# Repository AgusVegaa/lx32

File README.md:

<div align="center">
  <strong>PULSAR</strong><br>
  <em>LX32K keyboard processor stack: custom 32-bit core, RTL, golden model, LLVM backend, firmware, and host tools.</em>

  Overview | Firmware | Backend | RTL | Tools
</div>

This is the main source code repository for PULSAR. It contains the processor RTL, validation models, toolchain backend, firmware flow, and host utilities.

## Why PULSAR?

- **Determinism:** Hardware and firmware are designed for predictable timing and stable input scanning.
- **Full-stack control:** Custom ISA extensions, compiler backend, and simulation are all in one place.
- **Validation-first:** RTL, golden model, and tests keep behavior aligned across the stack.

## Quick Start

Run `make setup-backend`, then `make librust`.

## Getting Oriented

Start with `docs/README.md`, then `docs/firmware_guide.md` and `docs/backend.md`.

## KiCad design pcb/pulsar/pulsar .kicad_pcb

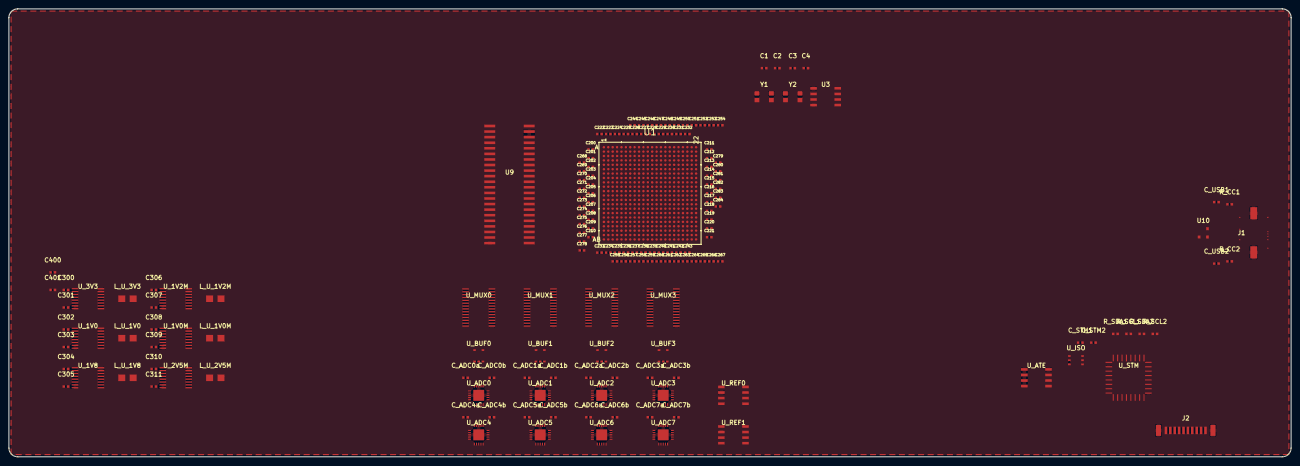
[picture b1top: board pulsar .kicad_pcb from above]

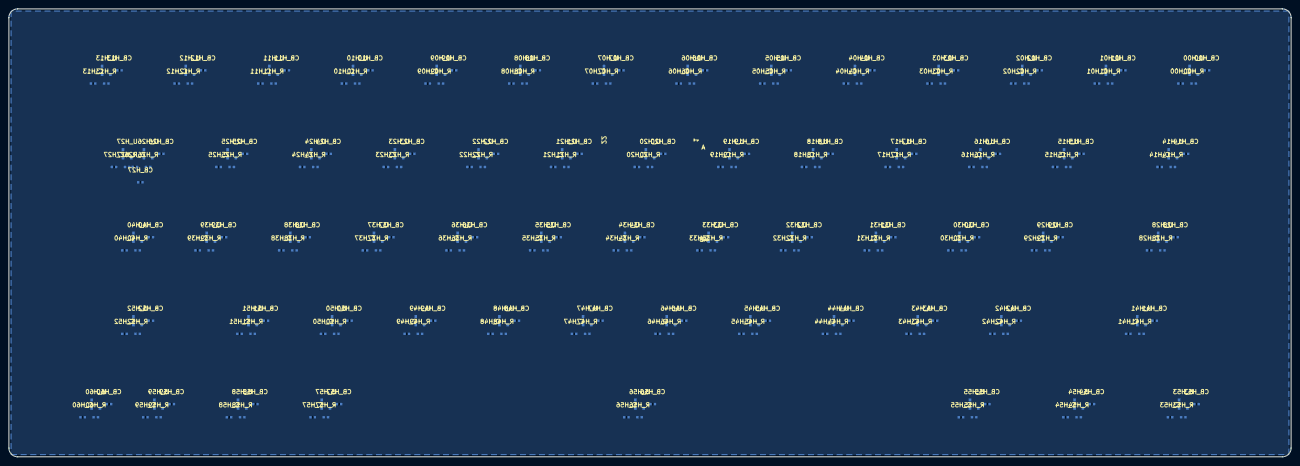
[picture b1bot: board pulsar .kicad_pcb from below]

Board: 16 copper layers, 292.0 x 102.0 mm, 414 parts (244 on the bottom side), 108 nets, no tracks yet.

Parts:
C1, C2, C3, C4: 12pF; C_0402
C200, C201, C202, C203, C204, C205, C206, C207, C208, C209, C210, C211, C212, C213, C214, C215, C216, C217, C218, C219, C220, C221, C222, C223, C224, C225, C226, C227, C228, C229, C230, C231, C232, C233, C234, C235, C236, C237, C238, C239, C240, C241, C242, C243, C244, C245, C246, C247, C248, C249, C250, C251, C252, C253, C254, C255, C256, C257, C258, C259, C260, C261, C262, C263, C264, C265, C266, C267, C268, C269, C270, C271, C272, C273, C274, C275, C276, C277, C278, C279, C280, C281, C282, C283, C284: 100nF; C_0402
C300, C302, C304, C306, C308, C310: 10uF 10V; C_0402
C301, C303, C305, C307, C309, C311: 10uF 6V; C_0402
C400, C401: 100uF 10V; C_0402
CB_H00, CB_H01, CB_H02, CB_H03, CB_H04, CB_H05, CB_H06, CB_H07, CB_H08, CB_H09, CB_H10, CB_H11, CB_H12, CB_H13, CB_H14, CB_H15, CB_H16, CB_H17, CB_H18, CB_H19, CB_H20, CB_H21, CB_H22, CB_H23, CB_H24, CB_H25, CB_H26, CB_H27, CB_H28, CB_H29, CB_H30, CB_H31, CB_H32, CB_H33, CB_H34, CB_H35, CB_H36, CB_H37, CB_H38, CB_H39, CB_H40, CB_H41, CB_H42, CB_H43, CB_H44, CB_H45, CB_H46, CB_H47, CB_H48, CB_H49, CB_H50, CB_H51, CB_H52, CB_H53, CB_H54, CB_H55, CB_H56, CB_H57, CB_H58, CB_H59, CB_H60: 100nF; C_0402
C_ADC0a, C_ADC1a, C_ADC2a, C_ADC3a, C_ADC4a, C_ADC5a, C_ADC6a, C_ADC7a: 100nF; C_0402
C_ADC0b, C_ADC1b, C_ADC2b, C_ADC3b, C_ADC4b, C_ADC5b, C_ADC6b, C_ADC7b: 1uF; C_0402
C_H00, C_H01, C_H02, C_H03, C_H04, C_H05, C_H06, C_H07, C_H08, C_H09, C_H10, C_H11, C_H12, C_H13, C_H14, C_H15, C_H16, C_H17, C_H18, C_H19, C_H20, C_H21, C_H22, C_H23, C_H24, C_H25, C_H26, C_H27, C_H28, C_H29, C_H30, C_H31, C_H32, C_H33, C_H34, C_H35, C_H36, C_H37, C_H38, C_H39, C_H40, C_H41, C_H42, C_H43, C_H44, C_H45, C_H46, C_H47, C_H48, C_H49, C_H50, C_H51, C_H52, C_H53, C_H54, C_H55, C_H56, C_H57, C_H58, C_H59, C_H60: 100nF; C_0402
C_STM1, C_STM2: 100nF; C_0402
C_USB1: 100nF; C_0402
C_USB2: 10uF; C_0402
J1: GX-C-065 USB-C; USB_C_Receptacle_HRO_TYPE-C-31-M-12
J2: FPC-10p 0.5mm; Molex_503480-1000_1x10-1MP_P1.00mm
L_U_1V0, L_U_1V0M, L_U_1V2M, L_U_1V8, L_U_2V5M, L_U_3V3: 2.2uH; L_2520_6332Metric
R_CC1, R_CC2: 5.1k; C_0402
R_H00, R_H01, R_H02, R_H03, R_H04, R_H05, R_H06, R_H07, R_H08, R_H09, R_H10, R_H11, R_H12, R_H13, R_H14, R_H15, R_H16, R_H17, R_H18, R_H19, R_H20, R_H21, R_H22, R_H23, R_H24, R_H25, R_H26, R_H27, R_H28, R_H29, R_H30, R_H31, R_H32, R_H33, R_H34, R_H35, R_H36, R_H37, R_H38, R_H39, R_H40, R_H41, R_H42, R_H43, R_H44, R_H45, R_H46, R_H47, R_H48, R_H49, R_H50, R_H51, R_H52, R_H53, R_H54, R_H55, R_H56, R_H57, R_H58, R_H59, R_H60: 10k; C_0402
R_SCL1, R_SCL2: 4.7k; C_0402
R_SDA1, R_SDA2: 4.7k; C_0402
U1: XC7A200T-2FBG484I; XC7A200T_FBG484
U3: W25Q128JVSIQ; SOIC-8_3.9x4.9mm_P1.27mm
U9: IS61WV102416BLL; SRAM_SOJ-44
U10: PRTR5V0U2X; SOT-23
U_1V0: TPS62130 +1V0; TSSOP-16_4.4x5mm_P0.65mm
U_1V0M: TPS62130 +1V0_MGT; TSSOP-16_4.4x5mm_P0.65mm
U_1V2M: TPS62130 +1V2_MGT; TSSOP-16_4.4x5mm_P0.65mm
U_1V8: TPS62130 +1V8; TSSOP-16_4.4x5mm_P0.65mm
U_2V5M: TPS62130 +2V5_MGT; TSSOP-16_4.4x5mm_P0.65mm
U_3V3: TPS62133 +3V3; TSSOP-16_4.4x5mm_P0.65mm
U_ADC0, U_ADC1, U_ADC2, U_ADC3, U_ADC4, U_ADC5, U_ADC6, U_ADC7: AD7689BCPZ; LFCSP-20-1EP_4x4mm_P0.5mm
U_ATE: ATECC608B-MAHDA-S; SOIC-8_3.9x4.9mm_P1.27mm
U_BUF0, U_BUF1, U_BUF2, U_BUF3: OPA2365AIDBVT; SOT-23-5
U_H00, U_H01, U_H02, U_H03, U_H04, U_H05, U_H06, U_H07, U_H08, U_H09, U_H10, U_H11, U_H12, U_H13, U_H14, U_H15, U_H16, U_H17, U_H18, U_H19, U_H20, U_H21, U_H22, U_H23, U_H24, U_H25, U_H26, U_H27, U_H28, U_H29, U_H30, U_H31, U_H32, U_H33, U_H34, U_H35, U_H36, U_H37, U_H38, U_H39, U_H40, U_H41, U_H42, U_H43, U_H44, U_H45, U_H46, U_H47, U_H48, U_H49, U_H50, U_H51, U_H52, U_H53, U_H54, U_H55, U_H56, U_H57, U_H58, U_H59, U_H60: DRV5055A2QDBZR; SOT-23
U_ISO: ISO1540QDRQ1; SOT-23-6
U_MUX0, U_MUX1, U_MUX2, U_MUX3: ADG1606BRUZ; TSSOP-28_4.4x9.7mm_P0.65mm
U_REF0, U_REF1: REF5025ID; SOIC-8_3.9x4.9mm_P1.27mm
U_STM: STM32L052K8T6; LQFP-32_7x7mm_P0.8mm
Y1: 50MHz_XTAL; Crystal_SMD_3225-4Pin_3.2x2.5mm
Y2: 48MHz_XTAL; Crystal_SMD_3225-4Pin_3.2x2.5mm

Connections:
+1V0: C200.1, C201.1, C202.1, C203.1, C204.1, C205.1, C206.1, C207.1, C208.1, C209.1, C210.1, C211.1, C212.1, C213.1, C214.1, C215.1, C216.1, C217.1, C218.1, C219.1, C220.1, C221.1, C222.1, C223.1, C224.1, C225.1, C226.1, C227.1, C249.1, C250.1, C251.1, C252.1, C253.1, C254.1, C303.1, L_U_1V0.2, U1.H8, U1.H10, U1.J7, U1.J9, U1.J11, U1.K8, U1.L7, U1.L11, U1.M8, U1.N7, U1.N11, U1.P8, U1.P10, U1.R7, U1.R9, U1.T8, U1.T10, U_1V0.9
+1V0_MGT: C237.1, C238.1, C239.1, C240.1, C268.1, C269.1, C270.1, C271.1, C272.1, C273.1, C279.1, C280.1, C281.1, C282.1, C283.1, C284.1, C309.1, L_U_1V0M.2, U1.D6, U1.D10, U1.E8, U1.F7, U1.F9, U_1V0M.9
+1V2_MGT: C241.1, C242.1, C243.1, C274.1, C275.1, C276.1, C277.1, C278.1, C307.1, L_U_1V2M.2, U1.B5, U1.B7, U1.B9, U1.B11, U1.C4, U1.C8, U_1V2M.9
+1V8: C233.1, C234.1, C235.1, C236.1, C262.1, C263.1, C264.1, C265.1, C266.1, C267.1, C305.1, C_STM2.1, L_U_1V8.2, R_SCL2.2, R_SDA2.2, U1.F12, U1.H12, U1.K10, U1.K12, U1.M12, U1.P12, U1.R11, U1.T12, U_1V8.9, U_ATE.7
+2V5_MGT: C255.1, C256.1, C257.1, C258.1, C259.1, C260.1, C261.1, C311.1, L_U_2V5M.2, U_2V5M.9
+2V5_REF: U_ADC0.7, U_ADC1.7, U_ADC2.7, U_ADC3.7, U_ADC4.7, U_ADC5.7, U_ADC6.7, U_ADC7.7, U_REF0.5, U_REF0.8, U_REF1.5, U_REF1.8
+3V3: C228.1, C229.1, C230.1, C231.1, C232.1, C244.1, C245.1, C246.1, C247.1, C248.1, C301.1, CB_H00.1, CB_H01.1, CB_H02.1, CB_H03.1, CB_H04.1, CB_H05.1, CB_H06.1, CB_H07.1, CB_H08.1, CB_H09.1, CB_H10.1, CB_H11.1, CB_H12.1, CB_H13.1, CB_H14.1, CB_H15.1, CB_H16.1, CB_H17.1, CB_H18.1, CB_H19.1, CB_H20.1, CB_H21.1, CB_H22.1, CB_H23.1, CB_H24.1, CB_H25.1, CB_H26.1, CB_H27.1, CB_H28.1, CB_H29.1, CB_H30.1, CB_H31.1, CB_H32.1, CB_H33.1, CB_H34.1, CB_H35.1, CB_H36.1, CB_H37.1, CB_H38.1, CB_H39.1, CB_H40.1, CB_H41.1, CB_H42.1, CB_H43.1, CB_H44.1, CB_H45.1, CB_H46.1, CB_H47.1, CB_H48.1, CB_H49.1, CB_H50.1, CB_H51.1, CB_H52.1, CB_H53.1, CB_H54.1, CB_H55.1, CB_H56.1, CB_H57.1, CB_H58.1, CB_H59.1, CB_H60.1, C_ADC0a.1, C_ADC0b.1, C_ADC1a.1, C_ADC1b.1, C_ADC2a.1, C_ADC2b.1, C_ADC3a.1, C_ADC3b.1, C_ADC4a.1, C_ADC4b.1, C_ADC5a.1, C_ADC5b.1, C_ADC6a.1, C_ADC6b.1, C_ADC7a.1, C_ADC7b.1, C_STM1.1, L_U_3V3.2, R_SCL1.2, R_SDA1.2, U1.A17, U1.AA7, U1.AA17, U1.AB4, U1.AB14, U1.B14, U1.C1, U1.C21, U1.D18, U1.E12, U1.E15, U1.F2, U1.F22, U1.G19, U1.H6, U1.H16, U1.J3, U1.J13, U1.K20, U1.L17, U1.M4, U1.M14, U1.N1, U1.N21, U1.P18, U1.R5, U1.R15, U1.T2, U1.T22, U1.U19, U1.V6, U1.V16, U1.W3, U1.W13, U1.Y10, U1.Y20, U3.2, U9.44, U_3V3.9, U_BUF0.5, U_BUF1.5, U_BUF2.5, U_BUF3.5, U_H00.3, U_H01.3, U_H02.3, U_H03.3, U_H04.3, U_H05.3, U_H06.3, U_H07.3, U_H08.3, U_H09.3, U_H10.3, U_H11.3, U_H12.3, U_H13.3, U_H14.3, U_H15.3, U_H16.3, U_H17.3, U_H18.3, U_H19.3, U_H20.3, U_H21.3, U_H22.3, U_H23.3, U_H24.3, U_H25.3, U_H26.3, U_H27.3, U_H28.3, U_H29.3, U_H30.3, U_H31.3, U_H32.3, U_H33.3, U_H34.3, U_H35.3, U_H36.3, U_H37.3, U_H38.3, U_H39.3, U_H40.3, U_H41.3, U_H42.3, U_H43.3, U_H44.3, U_H45.3, U_H46.3, U_H47.3, U_H48.3, U_H49.3, U_H50.3, U_H51.3, U_H52.3, U_H53.3, U_H54.3, U_H55.3, U_H56.3, U_H57.3, U_H58.3, U_H59.3, U_H60.3, U_ISO.6, U_MUX0.24, U_MUX1.24, U_MUX2.24, U_MUX3.24, U_REF0.1, U_REF0.4, U_REF0.6, U_REF1.1, U_REF1.4, U_REF1.6, U_STM.1, U_STM.32
ADC1_CNV: U_ADC0.4, U_ADC4.4
ADC1_SCK: U_ADC0.1, U_ADC4.1
ADC1_SDI: U_ADC0.3, U_ADC4.3
ADC1_SDO: U_ADC0.2, U_ADC4.2
ADC2_CNV: U_ADC1.4, U_ADC5.4
ADC2_SCK: U_ADC1.1, U_ADC5.1
ADC2_SDI: U_ADC1.3, U_ADC5.3
ADC2_SDO: U_ADC1.2, U_ADC5.2
ADC3_CNV: U_ADC2.4, U_ADC6.4
ADC3_SCK: U_ADC2.1, U_ADC6.1
ADC3_SDI: U_ADC2.3, U_ADC6.3
ADC3_SDO: U_ADC2.2, U_ADC6.2
ADC4_CNV: U_ADC3.4, U_ADC7.4
ADC4_SCK: U_ADC3.1, U_ADC7.1
ADC4_SDI: U_ADC3.3, U_ADC7.3
ADC4_SDO: U_ADC3.2, U_ADC7.2
CC1: J1.A5, R_CC1.1
CC2: J1.B8, R_CC2.1
CLK_48M: C3.1, C4.1, Y2.1, Y2.2
CLK_50M: C1.1, C2.1, Y1.1, Y1.2
FIDO2_SCL: R_SCL1.1, U_ISO.2, U_STM.29
FIDO2_SDA: R_SDA1.1, U_ISO.1, U_STM.30
GND: C1.2, C2.2, C3.2, C4.2, C200.2, C201.2, C202.2, C203.2, C204.2, C205.2, C206.2, C207.2, C208.2, C209.2, C210.2, C211.2, C212.2, C213.2, C214.2, C215.2, C216.2, C217.2, C218.2, C219.2, C220.2, C221.2, C222.2, C223.2, C224.2, C225.2, C226.2, C227.2, C228.2, C229.2, C230.2, C231.2, C232.2, C233.2, C234.2, C235.2, C236.2, C237.2, C238.2, C239.2, C240.2, C241.2, C242.2, C243.2, C244.2, C245.2, C246.2, C247.2, C248.2, C249.2, C250.2, C251.2, C252.2, C253.2, C254.2, C255.2, C256.2, C257.2, C258.2, C259.2, C260.2, C261.2, C262.2, C263.2, C264.2, C265.2, C266.2, C267.2, C268.2, C269.2, C270.2, C271.2, C272.2, C273.2, C274.2, C275.2, C276.2, C277.2, C278.2, C279.2, C280.2, C281.2, C282.2, C283.2, C284.2, C300.2, C301.2, C302.2, C303.2, C304.2, C305.2, C306.2, C307.2, C308.2, C309.2, C310.2, C311.2, C400.2, C401.2, CB_H00.2, CB_H01.2, CB_H02.2, CB_H03.2, CB_H04.2, CB_H05.2, CB_H06.2, CB_H07.2, CB_H08.2, CB_H09.2, CB_H10.2, CB_H11.2, CB_H12.2, CB_H13.2, CB_H14.2, CB_H15.2, CB_H16.2, CB_H17.2, CB_H18.2, CB_H19.2, CB_H20.2, CB_H21.2, CB_H22.2, CB_H23.2, CB_H24.2, CB_H25.2, CB_H26.2, CB_H27.2, CB_H28.2, CB_H29.2, CB_H30.2, CB_H31.2, CB_H32.2, CB_H33.2, CB_H34.2, CB_H35.2, CB_H36.2, CB_H37.2, CB_H38.2, CB_H39.2, CB_H40.2, CB_H41.2, CB_H42.2, CB_H43.2, CB_H44.2, CB_H45.2, CB_H46.2, CB_H47.2, CB_H48.2, CB_H49.2, CB_H50.2, CB_H51.2, CB_H52.2, CB_H53.2, CB_H54.2, CB_H55.2, CB_H56.2, CB_H57.2, CB_H58.2, CB_H59.2, CB_H60.2, C_ADC0a.2, C_ADC0b.2, C_ADC1a.2, C_ADC1b.2, C_ADC2a.2, C_ADC2b.2, C_ADC3a.2, C_ADC3b.2, C_ADC4a.2, C_ADC4b.2, C_ADC5a.2, C_ADC5b.2, C_ADC6a.2, C_ADC6b.2, C_ADC7a.2, C_ADC7b.2, C_H00.2, C_H01.2, C_H02.2, C_H03.2, C_H04.2, C_H05.2, C_H06.2, C_H07.2, C_H08.2, C_H09.2, C_H10.2, C_H11.2, C_H12.2, C_H13.2, C_H14.2, C_H15.2, C_H16.2, C_H17.2, C_H18.2, C_H19.2, C_H20.2, C_H21.2, C_H22.2, C_H23.2, C_H24.2, C_H25.2, C_H26.2, C_H27.2, C_H28.2, C_H29.2, C_H30.2, C_H31.2, C_H32.2, C_H33.2, C_H34.2, C_H35.2, C_H36.2, C_H37.2, C_H38.2, C_H39.2, C_H40.2, C_H41.2, C_H42.2, C_H43.2, C_H44.2, C_H45.2, C_H46.2, C_H47.2, C_H48.2, C_H49.2, C_H50.2, C_H51.2, C_H52.2, C_H53.2, C_H54.2, C_H55.2, C_H56.2, C_H57.2, C_H58.2, C_H59.2, C_H60.2, C_STM1.2, C_STM2.2, C_USB1.2, C_USB2.2, J1.A1, J1.A12, J1.B1, J1.B12, J1.SH1, J1.SH2, J2.MP1, J2.MP2, R_CC1.2, R_CC2.2, U1.A2, U1.A3, U1.A5, U1.A7, U1.A9, U1.A11, U1.A12, U1.A22, U1.AA2, U1.AA12, U1.AA22, U1.AB9, U1.AB19, U1.B3, U1.B12, U1.B19, U1.C3, U1.C6, U1.C10, U1.C12, U1.C16, U1.D3, U1.D4, U1.D8, U1.D12, U1.D13, U1.E4, U1.E5, U1.E7, U1.E9, U1.E11, U1.E20, U1.F5, U1.F11, U1.F17, U1.G5, U1.G6, U1.G7, U1.G8, U1.G9, U1.G10, U1.G12, U1.G14, U1.H1, U1.H7, U1.H9, U1.H11, U1.H21, U1.J8, U1.J10, U1.J12, U1.J18, U1.K5, U1.K7, U1.K9, U1.K11, U1.K15, U1.L2, U1.L8, U1.L9, U1.L22, U1.M7, U1.M11, U1.M19, U1.N6, U1.N8, U1.N16, U1.P3, U1.P7, U1.P9, U1.P11, U1.P13, U1.R8, U1.R10, U1.R12, U1.R20, U1.T7, U1.T9, U1.T11, U1.T17, U1.U4, U1.U14, U1.V1, U1.V11, U1.V21, U1.W8, U1.W18, U1.Y5, U1.Y15, U3.1, U3.4, U9.22, U9.42, U9.43, U10.2, U_1V0.7, U_1V0.8, U_1V0.15, U_1V0.16, U_1V0M.7, U_1V0M.8, U_1V0M.15, U_1V0M.16, U_1V2M.7, U_1V2M.8, U_1V2M.15, U_1V2M.16, U_1V8.7, U_1V8.8, U_1V8.15, U_1V8.16, U_2V5M.7, U_2V5M.8, U_2V5M.15, U_2V5M.16, U_3V3.7, U_3V3.8, U_3V3.15, U_3V3.16, U_ADC0.8, U_ADC0.11, U_ADC0.12, U_ADC0.13, U_ADC0.14, U_ADC0.15, U_ADC0.16, U_ADC0.17, U_ADC0.18, U_ADC0.EP, U_ADC1.8, U_ADC1.11, U_ADC1.12, U_ADC1.13, U_ADC1.14, U_ADC1.15, U_ADC1.16, U_ADC1.17, U_ADC1.18, U_ADC1.EP, U_ADC2.8, U_ADC2.11, U_ADC2.12, U_ADC2.13, U_ADC2.14, U_ADC2.15, U_ADC2.16, U_ADC2.17, U_ADC2.18, U_ADC2.EP, U_ADC3.8, U_ADC3.11, U_ADC3.12, U_ADC3.13, U_ADC3.14, U_ADC3.15, U_ADC3.16, U_ADC3.17, U_ADC3.18, U_ADC3.EP, U_ADC4.8, U_ADC4.11, U_ADC4.12, U_ADC4.13, U_ADC4.14, U_ADC4.15, U_ADC4.16, U_ADC4.17, U_ADC4.18, U_ADC4.EP, U_ADC5.8, U_ADC5.11, U_ADC5.12, U_ADC5.13, U_ADC5.14, U_ADC5.15, U_ADC5.16, U_ADC5.17, U_ADC5.18, U_ADC5.EP, U_ADC6.8, U_ADC6.11, U_ADC6.12, U_ADC6.13, U_ADC6.14, U_ADC6.15, U_ADC6.16, U_ADC6.17, U_ADC6.18, U_ADC6.EP, U_ADC7.8, U_ADC7.11, U_ADC7.12, U_ADC7.13, U_ADC7.14, U_ADC7.15, U_ADC7.16, U_ADC7.17, U_ADC7.18, U_ADC7.EP, U_ATE.1, U_ATE.2, U_ATE.3, U_ATE.4, U_ATE.8, U_BUF0.2, U_BUF1.2, U_BUF2.2, U_BUF3.2, U_H00.2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
HALL0: R_H00.1, U_H00.1, U_MUX0.1
HALL1: R_H01.1, U_H01.1, U_MUX0.2
HALL2: R_H02.1, U_H02.1, U_MUX0.3
HALL3: R_H03.1, U_H03.1, U_MUX0.4
HALL4: R_H04.1, U_H04.1, U_MUX0.5
HALL5: R_H05.1, U_H05.1, U_MUX0.6
HALL6: R_H06.1, U_H06.1, U_MUX0.7
HALL7: R_H07.1, U_H07.1, U_MUX0.8
HALL8: R_H08.1, U_H08.1, U_MUX0.9
HALL9: R_H09.1, U_H09.1, U_MUX0.10
HALL10: R_H10.1, U_H10.1, U_MUX0.11
HALL11: R_H11.1, U_H11.1, U_MUX0.12
HALL12: R_H12.1, U_H12.1, U_MUX0.13
HALL13: R_H13.1, U_H13.1, U_MUX0.14
HALL14: R_H14.1, U_H14.1, U_MUX0.16
HALL15: R_H15.1, U_H15.1, U_MUX0.17
HALL16: R_H16.1, U_H16.1, U_MUX1.1
HALL17: R_H17.1, U_H17.1, U_MUX1.2
HALL18: R_H18.1, U_H18.1, U_MUX1.3
HALL19: R_H19.1, U_H19.1, U_MUX1.4
HALL20: R_H20.1, U_H20.1, U_MUX1.5
HALL21: R_H21.1, U_H21.1, U_MUX1.6
HALL22: R_H22.1, U_H22.1, U_MUX1.7
HALL23: R_H23.1, U_H23.1, U_MUX1.8
HALL24: R_H24.1, U_H24.1, U_MUX1.9
HALL25: R_H25.1, U_H25.1, U_MUX1.10
HALL26: R_H26.1, U_H26.1, U_MUX1.11
HALL27: R_H27.1, U_H27.1, U_MUX1.12
HALL28: R_H28.1, U_H28.1, U_MUX1.13
HALL29: R_H29.1, U_H29.1, U_MUX1.14
HALL30: R_H30.1, U_H30.1, U_MUX1.16
HALL31: R_H31.1, U_H31.1, U_MUX1.17
HALL32: R_H32.1, U_H32.1, U_MUX2.1
HALL33: R_H33.1, U_H33.1, U_MUX2.2
HALL34: R_H34.1, U_H34.1, U_MUX2.3
HALL35: R_H35.1, U_H35.1, U_MUX2.4
HALL36: R_H36.1, U_H36.1, U_MUX2.5
HALL37: R_H37.1, U_H37.1, U_MUX2.6
HALL38: R_H38.1, U_H38.1, U_MUX2.7
HALL39: R_H39.1, U_H39.1, U_MUX2.8
HALL40: R_H40.1, U_H40.1, U_MUX2.9
HALL41: R_H41.1, U_H41.1, U_MUX2.10
HALL42: R_H42.1, U_H42.1, U_MUX2.11
HALL43: R_H43.1, U_H43.1, U_MUX2.12
HALL44: R_H44.1, U_H44.1, U_MUX2.13
HALL45: R_H45.1, U_H45.1, U_MUX2.14
HALL46: R_H46.1, U_H46.1, U_MUX2.16
HALL47: R_H47.1, U_H47.1, U_MUX2.17
HALL48: R_H48.1, U_H48.1, U_MUX3.1
HALL49: R_H49.1, U_H49.1, U_MUX3.2
HALL50: R_H50.1, U_H50.1, U_MUX3.3
HALL51: R_H51.1, U_H51.1, U_MUX3.4
HALL52: R_H52.1, U_H52.1, U_MUX3.5
HALL53: R_H53.1, U_H53.1, U_MUX3.6
HALL54: R_H54.1, U_H54.1, U_MUX3.7
HALL55: R_H55.1, U_H55.1, U_MUX3.8
HALL56: R_H56.1, U_H56.1, U_MUX3.9
HALL57: R_H57.1, U_H57.1, U_MUX3.10
HALL58: R_H58.1, U_H58.1, U_MUX3.11
HALL59: R_H59.1, U_H59.1, U_MUX3.12
HALL60: R_H60.1, U_H60.1, U_MUX3.13
I2C_SCL: R_SCL2.1, U_ATE.5, U_ISO.4
I2C_SDA: R_SDA2.1, U_ATE.6, U_ISO.5
MUX0_D: U_BUF0.3, U_MUX0.23
MUX0_OUT: U_ADC0.9, U_ADC4.9, U_BUF0.1, U_BUF0.4
MUX1_D: U_BUF1.3, U_MUX1.23
MUX1_OUT: U_ADC1.9, U_ADC5.9, U_BUF1.1, U_BUF1.4
MUX2_D: U_BUF2.3, U_MUX2.23
MUX2_OUT: U_ADC2.9, U_ADC6.9, U_BUF2.1, U_BUF2.4
MUX3_D: U_BUF3.3, U_MUX3.23
MUX3_OUT: U_ADC3.9, U_ADC7.9, U_BUF3.1, U_BUF3.4
MUX_A0: U_MUX0.18, U_MUX1.18, U_MUX2.18, U_MUX3.18
MUX_A1: U_MUX0.19, U_MUX1.19, U_MUX2.19, U_MUX3.19
MUX_A2: U_MUX0.20, U_MUX1.20, U_MUX2.20, U_MUX3.20
MUX_A3: U_MUX0.21, U_MUX1.21, U_MUX2.21, U_MUX3.21
USB_DM_RAW: J1.A7, J1.B7, U10.3, U_STM.18
USB_DP_RAW: J1.A6, J1.B6, U10.1, U_STM.19
VBUS: C300.1, C302.1, C304.1, C306.1, C308.1, C310.1, C400.1, C401.1, C_USB1.1, C_USB2.1, J1.A4, J1.B9, L_U_1V0.1, L_U_1V0M.1, L_U_1V2M.1, L_U_1V8.1, L_U_2V5M.1, L_U_3V3.1, U_1V0.1, U_1V0M.1, U_1V2M.1, U_1V8.1, U_2V5M.1, U_3V3.1

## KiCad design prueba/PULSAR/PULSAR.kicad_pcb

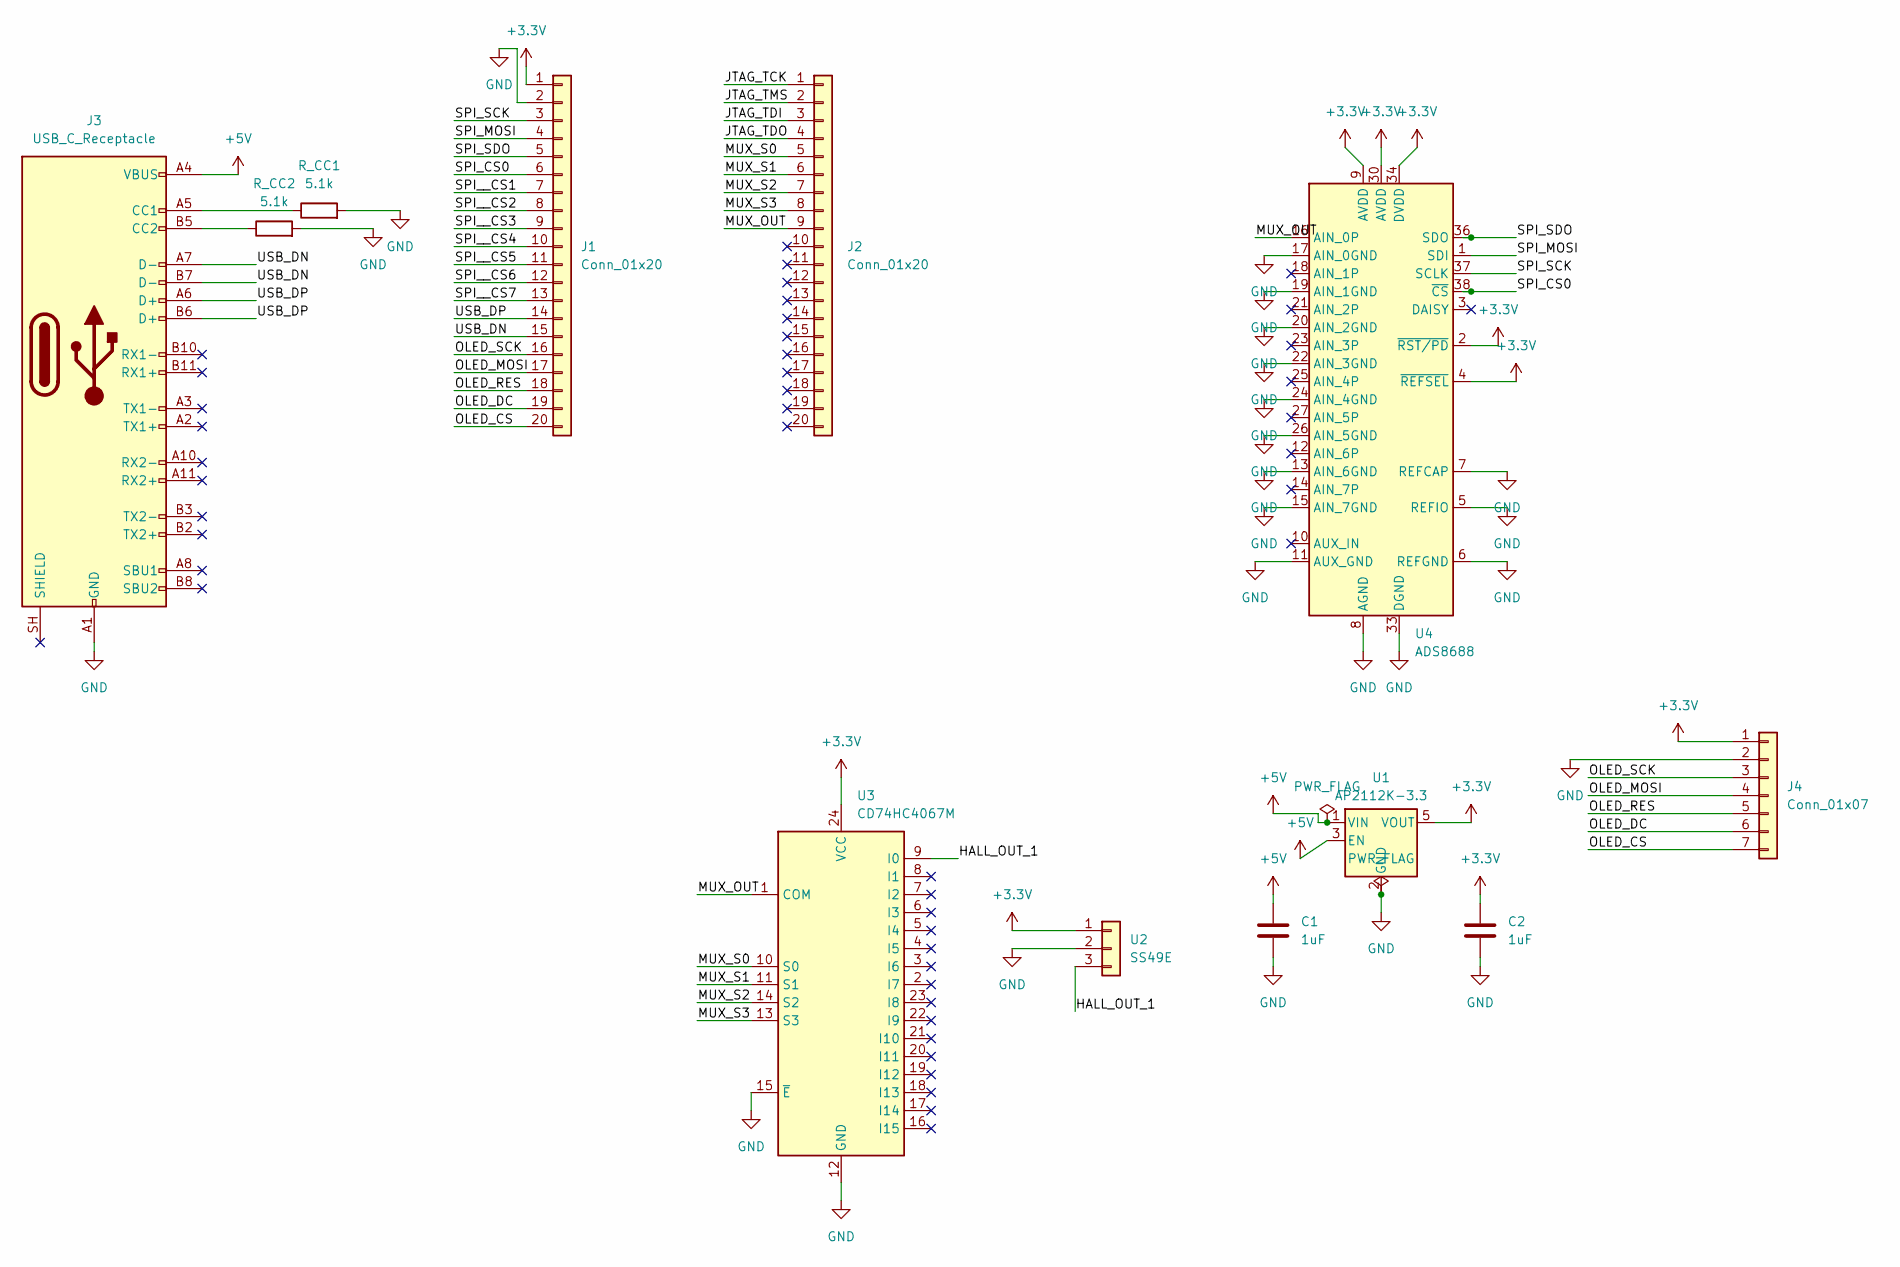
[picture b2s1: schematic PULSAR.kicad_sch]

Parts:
C1, C2: 1uF; C_0805_2012Metric; LCSC C52923
J1, J2: Conn_01x20; PinHeader_1x20_P2.54mm_Vertical
J3: USB_C_Receptacle; USB_C_Receptacle_GCT_USB4115-03-C; LCSC C168688
J4: Conn_01x07; PinHeader_1x07_P2.54mm_Vertical
R_CC1, R_CC2: 5.1k; R_0402_1005Metric; LCSC C23186
U1: AP2112K-3.3; SOT-23-5; LCSC C51118
U2: SS49E; TO-92_Inline; LCSC C85697
U3: CD74HC4067M; SSOP-24_5.3x8.2mm_P0.65mm; LCSC C98457
U4: ADS8688; TSSOP-38_4.4x9.7mm_P0.5mm; LCSC C1542682

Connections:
+3.3V: C2.1, J1.1, J4.1, U1.5 (VOUT), U2.1, U3.24 (VCC), U4.2 (~RST/PD), U4.4 (~REFSEL), U4.9 (AVDD), U4.30 (AVDD), U4.34 (DVDD)
+5V: C1.1, J3.A4 (VBUS), J3.A9 (VBUS), J3.B4 (VBUS), J3.B9 (VBUS), U1.1 (VIN), U1.3 (EN)
/HALL_OUT_1: U2.3, U3.9 (I0)
/JTAG_TCK: J2.1
/JTAG_TDI: J2.3
/JTAG_TDO: J2.4
/JTAG_TMS: J2.2
/MUX_OUT: J2.9, U3.1 (COM), U4.16 (AIN_0P)
/MUX_S0: J2.5, U3.10 (S0)
/MUX_S1: J2.6, U3.11 (S1)
/MUX_S2: J2.7, U3.14 (S2)
/MUX_S3: J2.8, U3.13 (S3)
/OLED_CS: J1.20, J4.7
/OLED_DC: J1.19, J4.6
/OLED_MOSI: J1.17, J4.4
/OLED_RES: J1.18, J4.5
/OLED_SCK: J1.16, J4.3
/SPI_CS0: J1.6, U4.38 (~CS)
/SPI_MOSI: J1.4, U4.1 (SDI)
/SPI_SCK: J1.3, U4.37 (SCLK)
/SPI_SDO: J1.5, U4.36 (SDO)
/SPI__CS1: J1.7
/SPI__CS2: J1.8
/SPI__CS3: J1.9
/SPI__CS4: J1.10
/SPI__CS5: J1.11
/SPI__CS6: J1.12
/SPI__CS7: J1.13
/USB_DN: J1.15, J3.A7 (D-), J3.B7 (D-)
/USB_DP: J1.14, J3.A6 (D+), J3.B6 (D+)
GND: C1.2, C2.2, J1.2, J3.A1 (GND), J3.A12 (GND), J3.B1 (GND), J3.B12 (GND), J4.2, R_CC1.2, R_CC2.2, U1.2 (GND), U2.2, U3.12 (GND), U3.15 (~E), U4.5 (REFIO), U4.6 (REFGND), U4.7 (REFCAP), U4.8 (AGND), U4.11 (AUX_GND), U4.13 (AIN_6GND), U4.15 (AIN_7GND), U4.17 (AIN_0GND), U4.19 (AIN_1GND), U4.20 (AIN_2GND), U4.22 (AIN_3GND), U4.24 (AIN_4GND), U4.26 (AIN_5GND), U4.28 (AGND), U4.29 (AGND), U4.31 (AGND), U4.32 (AGND), U4.33 (DGND)
unnamed: J3.A5 (CC1), R_CC1.1
unnamed: J3.B5 (CC2), R_CC2.1

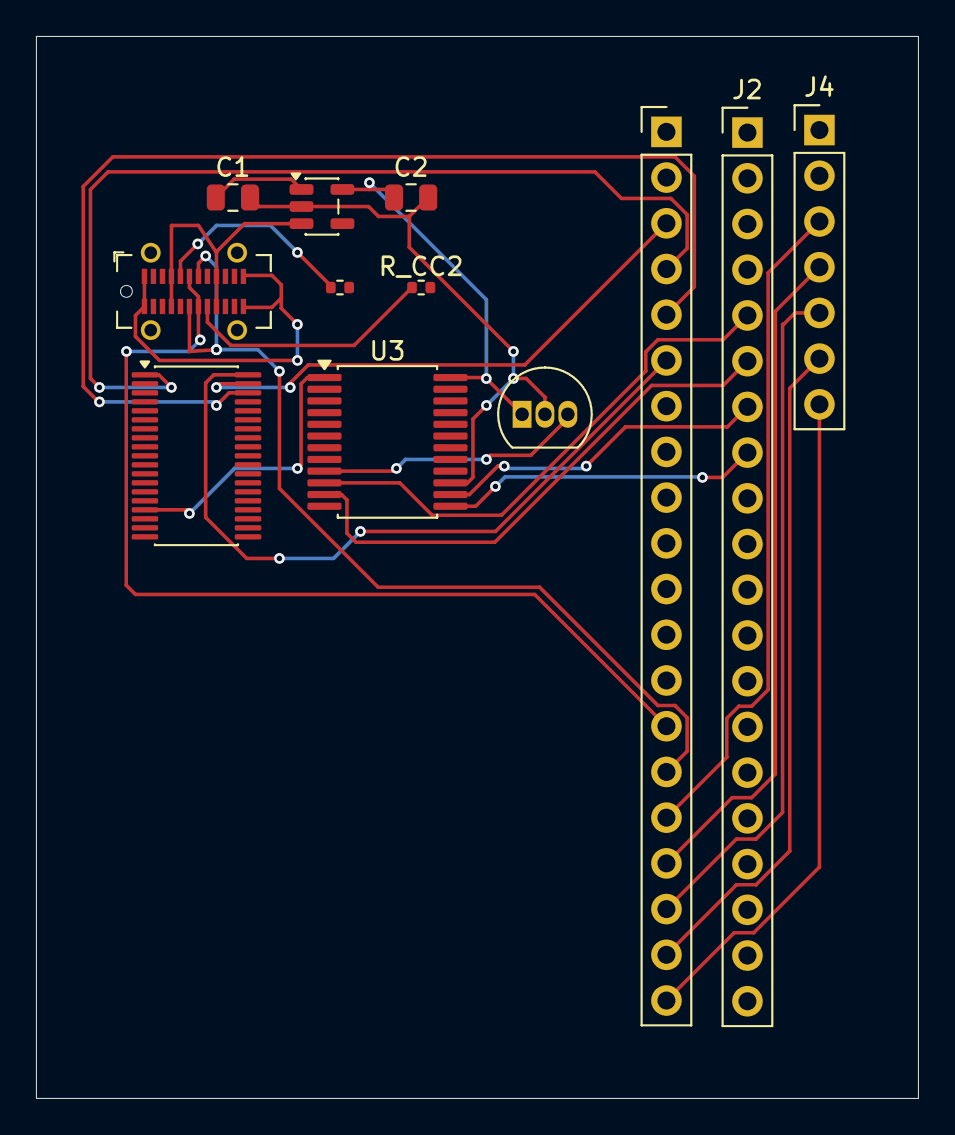
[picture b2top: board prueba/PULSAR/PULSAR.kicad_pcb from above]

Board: 4 copper layers, 49.0 x 59.0 mm, 12 parts (0 on the bottom side), 22 nets.

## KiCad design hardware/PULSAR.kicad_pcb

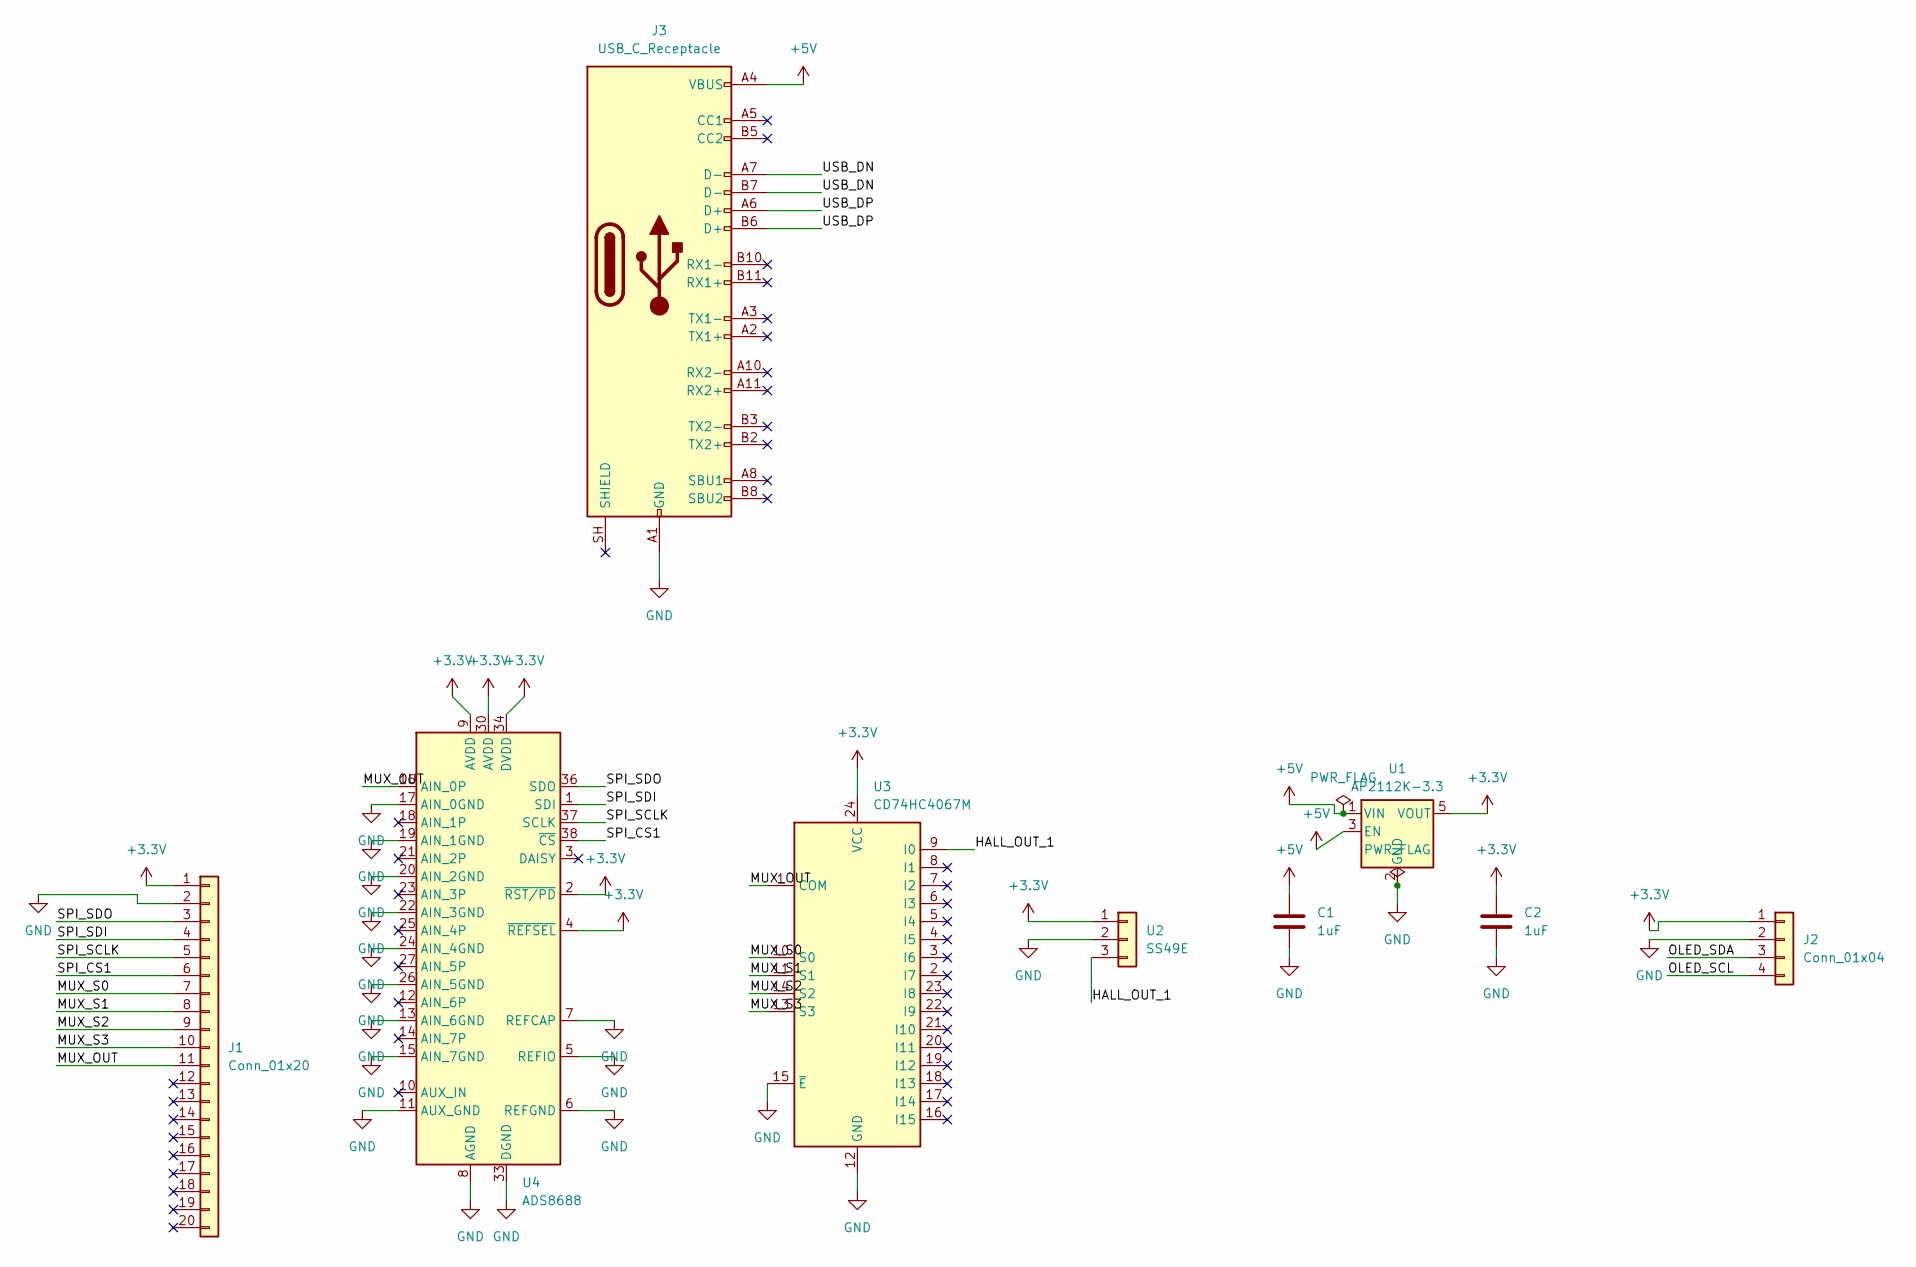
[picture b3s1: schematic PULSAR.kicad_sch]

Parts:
C1, C2: 1uF; C_0805_2012Metric
J1: Conn_01x20; PinHeader_1x20_P2.54mm_Vertical
J2: Conn_01x04; PinHeader_1x04_P2.54mm_Vertical
J3: USB_C_Receptacle; USB_C_Receptacle_GCT_USB4115-03-C
U1: AP2112K-3.3; SOT-23-5
U2: SS49E; TO-92_Inline
U3: CD74HC4067M; SOIC-24W_7.5x15.4mm_P1.27mm
U4: ADS8688; TSSOP-38_4.4x9.7mm_P0.5mm

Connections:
+3.3V: C2.1, J1.1, J2.1, U1.5 (VOUT), U2.1, U3.24 (VCC), U4.2 (~RST/PD), U4.4 (~REFSEL), U4.9 (AVDD), U4.30 (AVDD), U4.34 (DVDD)
+5V: C1.1, J3.A4 (VBUS), J3.A9 (VBUS), J3.B4 (VBUS), J3.B9 (VBUS), U1.1 (VIN), U1.3 (EN)
/HALL_OUT_1: U2.3, U3.9 (I0)
/MUX_OUT: J1.11, U3.1 (COM), U4.16 (AIN_0P)
/MUX_S0: J1.7, U3.10 (S0)
/MUX_S1: J1.8, U3.11 (S1)
/MUX_S2: J1.9, U3.14 (S2)
/MUX_S3: J1.10, U3.13 (S3)
/OLED_SCL: J2.4
/OLED_SDA: J2.3
/SPI_CS1: J1.6, U4.38 (~CS)
/SPI_SCLK: J1.5, U4.37 (SCLK)
/SPI_SDI: J1.4, U4.1 (SDI)
/SPI_SDO: J1.3, U4.36 (SDO)
/USB_DN: J3.A7 (D-), J3.B7 (D-)
/USB_DP: J3.A6 (D+), J3.B6 (D+)
GND: C1.2, C2.2, J1.2, J2.2, J3.A1 (GND), J3.A12 (GND), J3.B1 (GND), J3.B12 (GND), U1.2 (GND), U2.2, U3.12 (GND), U3.15 (~E), U4.5 (REFIO), U4.6 (REFGND), U4.7 (REFCAP), U4.8 (AGND), U4.11 (AUX_GND), U4.13 (AIN_6GND), U4.15 (AIN_7GND), U4.17 (AIN_0GND), U4.19 (AIN_1GND), U4.20 (AIN_2GND), U4.22 (AIN_3GND), U4.24 (AIN_4GND), U4.26 (AIN_5GND), U4.28 (AGND), U4.29 (AGND), U4.31 (AGND), U4.32 (AGND), U4.33 (DGND)

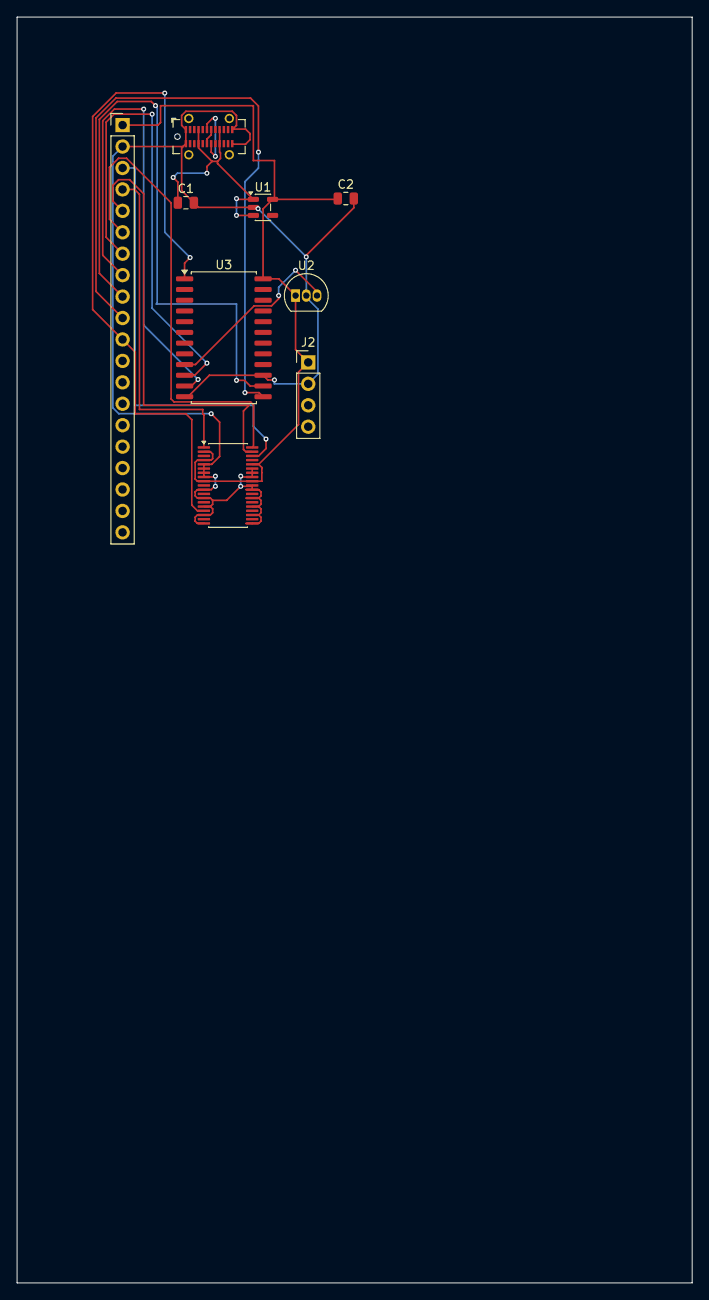
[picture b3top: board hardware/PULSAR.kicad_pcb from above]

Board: 4 copper layers, 80.0 x 150.0 mm, 9 parts (0 on the bottom side), 15 nets.

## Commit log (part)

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2026-03-08 Update .gitignore with additional ignored files (#52)
    Add default ignored files and folders to .gitignore
2026-03-15 Enhance README with project details and structure (#68)
    Expanded project description and clarified goals, architecture, and verification processes. Added detailed sections on validation commands and documentation structure.
2026-03-15 Document repository structure in README (#69)
    Added repository structure section with detailed file layout.
2026-03-17 Enhance README with project overview and objectives (#70)
    Expanded project description to clarify goals and approach.
2026-04-01 Refactor/tablegen patterns pseudos (#73)
    * feat(tablegen): fix pointer regclass mapping and pseudo overrides
    - Added RemapAllTargetPseudoPointerOperands to fix ptr_rc errors.
    - Fixed instruction property inference (mayLoad/mayStore).
    - Organized includes and fixed Pseudo class scope.
    - Added compile_td.sh utility script.
    * fix(tablegen): correct four bugs found in Day 3 review
2026-04-01 feat: added Subtarget in the script to generate an .inc file (#75)
2026-04-01 Feat/llvm backend subtarget stubs (#76)
    * feat: added Subtarget in the script to generate an .inc file
    * feat: add minimal Subtarget and TargetMachine stubs
    - Register Subtarget/TargetMachine sources in LX32CodeGen CMake target
    - Provide minimal buildable LX32Subtarget and LX32TargetMachine skeletons
    - Add placeholder headers for lowering/frame/reg/instr info (stubs)
2026-04-05 Feat/formal verification (#79)
    * formal: add end-to-end closure gate, harden tool checks, and publish full ISA equation model
    - add formal CI workflow with closure-proof gate (coq + sva/lec + seeded lockstep)\n- enforce deterministic seeded validation by requiring SEED for validate-seed\n- strengthen setup dependency checks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
    * chore: commit remaining rtl, tb, validator, and ci updates
    - include remaining wo
2026-04-06 Feature/lx32 validator runner (#82)
    * fix(lx32-backend): support unconditional branch selection
    * feat(validator): add binary runner for RTL simulation
    * Fix: correct fixup creation, ELF relocation mapping, and Makefile for CI and backend correctness
2026-04-09 Revise README for PULSAR project details
    Updated the README to reflect the PULSAR project and its features, including architecture, verification, and documentation.
2026-04-09 chore: add @AgusVeega to the codeowners file
2026-04-09 docs: added initial docs for common baseline
2026-04-10 feat: add MUX CD74HC4067M schematic with control signals
2026-04-10 refactor: decouple LLVM build, fix TableGen integration and backend paths
2026-04-10 sync: import backend build + TableGen integration from Pulsar (#88)
2026-04-10 feat: add power section schematic AP2112K-3.3 LDO 5V to 3.3V (#4)
    * feat: add power section schematic AP2112K-3.3 LDO 5V to 3.3V
    * feat: add Hall sensor SS49E schematic with HALL_OUT_1 net
    * feat: add MUX CD74HC4067M schematic with control signals
    * feat: add ADS8688 ADC schematic with SPI signals and analog input from MUX
    * feat: add OrangeCrab connector with SPI, MUX and power signals
    * feat: add OLED SSD1306 connector with SPI signals
2026-04-11 ci: add backend toolchain artifacts and runtime-only image flow
2026-04-11 ci: add docker context preflight check before backend image build
2026-04-11 build: generate LX32 TableGen .inc files during docker build
2026-04-11 ci: fix ld.lld artifact extraction (dereference symlink)
2026-04-12 ci: optimize backend pipeline with buildx cache and branch-gated runtime publish
2026-04-12 ci: lowercase GHCR owner in image tags
2026-04-12 feat: generate gerber files for JLCPCB manufacturing
2026-04-12 ci: add llc preflight gate and fix LX32 TableGen include path
2026-04-12 tests: fix sed in-place handling for Linux preflight
2026-04-12 lx32/tests: fix baremetal scripts for repo-relative paths in CI
2026-04-12 lx32/isel: materialize BRCC constants via generic DAG add
2026-04-12 ci: pin LLVM ref and verify backend commit in deep preflight
2026-04-12 docker: allow LLVM_REF to be branch or commit SHA
2026-04-12 ci: make deep baremetal preflight advisory
2026-04-12 Fix operand order for BR and BRCC in ISel to avoid Segfault in llc
2026-04-12 Fix CurDAG typo in SelectionDAG for CALL instruction
2026-04-12 Improve Docker cache reuse and ccache visibility
2026-04-12 no cache
2026-04-12 ci: bust stale cache scope for lx32-runtime
2026-04-13 CI/runtime split + LX32 backend stabilization (#5)
    * chore: change the clone command with the custom llvm fork
    * refactor: decouple LLVM build, fix TableGen integration and backend paths
    * sync: import backend build + TableGen integration from Pulsar (#88)
    * ci: add backend toolchain artifacts and runtime-only image flow
    * build: add docker build context files required by CI workflow
    * ci: add docker context preflight check before backend image build
2026-04-13 Kicad (#6)
    * feat: add power section schematic AP2112K-3.3 LDO 5V to 3.3V
    * feat: add Hall sensor SS49E schematic with HALL_OUT_1 net
    * feat: add MUX CD74HC4067M schematic with control signals
    * feat: add ADS8688 ADC schematic with SPI signals and analog input from MUX
    * feat: add OrangeCrab connector with SPI, MUX and power signals
    * feat: add OLED SSD1306 connector with SPI signals
2026-04-13 docs: added initial documentation of technical backend decisions (#7)
2026-04-13 Clean up README content
    Removed excessive and unclear text from README.
2026-04-13 Clean up README content (#8)
    Removed excessive and unclear text from README.
2026-04-16 feat: implement custom keyboard instructions and fix lx.wait timing
2026-04-16 Feat/custom instructions (#9)
    * feat: full integration of LX custom ISA and hardware controllers
    * feat: update gitignore and add benchmark summary tools
    * feat: implement custom keyboard instructions and fix lx.wait timing
    * feat: add intrinsics for lx32k custom isa and rust target spec
    * docs: add pulsar-pac and comprehensive firmware development guide
2026-04-19 feat(lx32): add custom instructions support and cleanup pulsar_pac
2026-04-22 feat: PCB routing in progress - power and SPI connections
2026-04-26 Feat/custom instructions (#10)
    * feat: full integration of LX custom ISA and hardware controllers
    * feat: update gitignore and add benchmark summary tools
    * feat: implement custom keyboard instructions and fix lx.wait timing
    * feat: add intrinsics for lx32k custom isa and rust target spec
    * docs: add pulsar-pac and comprehensive firmware development guide
    * feat(lx32): add custom instructions support and cleanup pulsar_pac
2026-05-03 Initial plan
2026-05-03 fix(lx32-backend): restore setup and custom bench builds (#14)
    Remove duplicated DAG selector declarations/definitions, make intrinsic lowering resolve lx32 intrinsics by base name, and add builtin-aware fallback wrappers for custom intrinsics used by baremetal 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
2026-05-03 chore(deps): bump rand from 0.10.0 to 0.10.1 in /tools/lx32_validator
    Bumps [rand](https://github.com/rust-random/rand) from 0.10.0 to 0.10.1.
    - [Release notes](https://github.com/rust-random/rand/releases)
    - [Changelog](https://github.com/rust-random/rand/blob/master/CHANGELOG.md)
    - [Commits](https://github.com/rust-random/rand/compare/0.10.0...0.10.1)
    ---
    updated-dependencies:
2026-05-03 chore(deps): bump rand from 0.10.0 to 0.10.1 in /tools/lx32_validator (#15)
    Bumps [rand](https://github.com/rust-random/rand) from 0.10.0 to 0.10.1.
    - [Release notes](https://github.com/rust-random/rand/releases)
    - [Changelog](https://github.com/rust-random/rand/blob/master/CHANGELOG.md)
    - [Commits](https://github.com/rust-random/rand/compare/0.10.0...0.10.1)
    ---
    updated-dependencies:
2026-05-03 refactor: changed the core to be more roboust
2026-05-03 refactor: changed the core to be more roboust (#16)
2026-05-03 Add Angel to the team section of README
2026-05-04 feat(lx32): backend fixup/softfloat updates, PAC improvements, Rust firmware tests
    - lx32_backend: hi20/lo12_i fixups, PseudoLA guard, BSWAP/CTTZ/BR_JT ops, f16/f128 expansion, CTLZ/CTPOP libcall wiring
    - target JSON: updated lx32-unknown-none-elf spec
    - tests/baremetal: update crt0, link script, Rust firmware programs (fibonacci, custom intrinsics)
    - pulsar_pac: update Cargo.toml, cargo config, keyboard example, raw/runtime sources
    - Makefile: build target updates
2026-05-06 fix(pac): static mut warning cleanup
    Use raw-pointer access via addr_of_mut! in keyboard/frame_budget examples to avoid static_mut_refs warnings.
2026-05-10 refactor: initial cleanup to start
2026-05-10 feat(pcb): power supply schematic complete — U1-U6 buck+LDO rails
2026-05-10 feat(pcb): FPGA A1 schematic complete — MGT, ADC0-7 pinout, MUX sel
2026-05-10 feat(pcb): FPGA schematic structure — full pinout A1, hierarchy reorganized
2026-05-11 feat: added the pcb of the pulsar
2026-05-11 fix: separation of overlapped components
2026-05-11 Feat/pcb for pulsar (#24)
    * refactor: initial cleanup to start
    * feat(pcb): power supply schematic complete — U1-U6 buck+LDO rails
    * feat(pcb): FPGA A1 schematic complete — MGT, ADC0-7 pinout, MUX sel
    * feat(pcb): FPGA schematic structure — full pinout A1, hierarchy reorganized
    * feat: added the pcb of the pulsar
    * fix: separation of overlapped components
2026-05-19 chore: renamed 'pulsar ' to 'pulsar'
2026-05-19 chore: renamed 'pulsar ' to 'pulsar' (#25)
2026-05-19 Configurar DRC, layers y tamaños de pista
2026-05-19 Update pulsar .kicad_prl numeric entries
    Adjust several numeric values in pcb/pulsar/pulsar .kicad_prl (updated entries around the listed numeric array). Also remove the stale temporary KiCad lock file pcb/pulsar/~pulsar .kicad_pcb.lck.
2026-05-20 feat: let everything to route
2026-05-20 Feat/config layers (#26)
    * Configurar DRC, layers y tamaños de pista
    * Update pulsar .kicad_prl numeric entries
    Adjust several numeric values in pcb/pulsar/pulsar .kicad_prl (updated entries around the listed numeric array). Also remove the stale temporary KiCad lock file pcb/pulsar/~pulsar .kicad_pcb.lck.
    * feat: let everything to route
    ---------
2026-05-23 refactor: I deleted all the pcb and documents from lithos and routing to start from scratch
2026-05-23 docs: added small readme
2026-05-23 docs: added small readme (#29)
2026-05-31 create com.kicad
    In this folder I explain the components that I am going to use in Kicad.
2026-06-01 create com.kicad (#30)
    In this folder I explain the components that I am going to use in Kicad.
